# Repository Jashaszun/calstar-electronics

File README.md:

# calstar-electronics
The overall repository for CalSTAR-related hardware, firmware, software, and electronics documentation.

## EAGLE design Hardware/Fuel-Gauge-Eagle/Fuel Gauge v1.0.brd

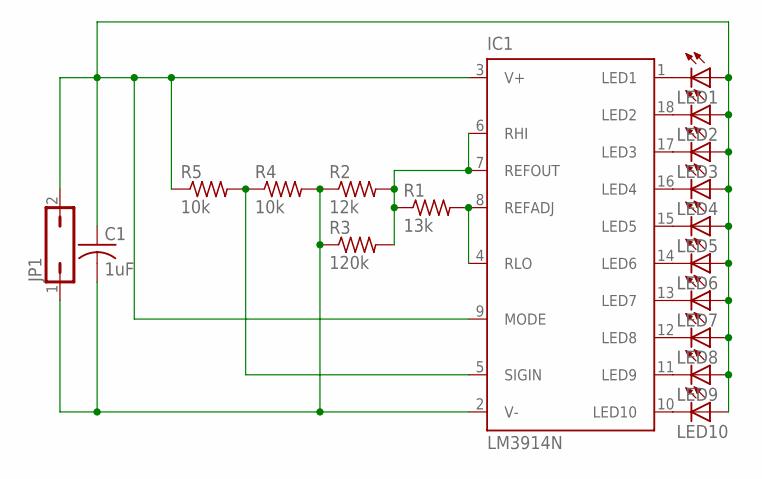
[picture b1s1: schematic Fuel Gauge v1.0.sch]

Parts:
C1: 1uF; C0603
IC1: LM3914N; DIL18
JP1: JP1Q; JP1
LED1, LED2, LED3, LED4, LED5, LED6, LED7, LED8, LED9, LED10: LEDCHIPLED_0603; CHIPLED_0603
R1: 13k; R0603
R2: 12k; R0603
R3: 120k; R0603
R4, R5: 10k; R0603

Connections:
GND: C1.2, IC1.2 (V-), JP1.1, R2.1, R3.1, R4.2
LED1: IC1.1 (LED1), LED1.C
LED2: IC1.18 (LED2), LED2.C
LED3: IC1.17 (LED3), LED3.C
LED4: IC1.16 (LED4), LED4.C
LED5: IC1.15 (LED5), LED5.C
LED6: IC1.14 (LED6), LED6.C
LED7: IC1.13 (LED7), LED7.C
LED8: IC1.12 (LED8), LED8.C
LED9: IC1.11 (LED9), LED9.C
LED10: IC1.10 (LED10), LED10.C
REFADJ/RLO: IC1.4 (RLO), IC1.8 (REFADJ), R1.2
REFOUT/RHI: IC1.6 (RHI), IC1.7 (REFOUT), R1.1, R2.2, R3.2
SIGIN: IC1.5 (SIGIN), R4.1, R5.2
VBATT: C1.1, IC1.3 (V+), IC1.9 (MODE), JP1.2, LED1.A, LED2.A, LED3.A, LED4.A, LED5.A, LED6.A, LED7.A, LED8.A, LED9.A, LED10.A, R5.1

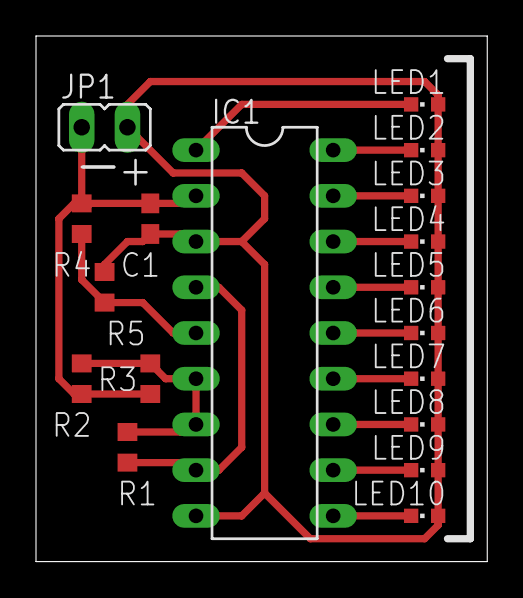
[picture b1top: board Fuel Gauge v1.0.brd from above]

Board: 2 copper layers, 25.1 x 29.2 mm, 18 parts (0 on the bottom side), 15 nets.

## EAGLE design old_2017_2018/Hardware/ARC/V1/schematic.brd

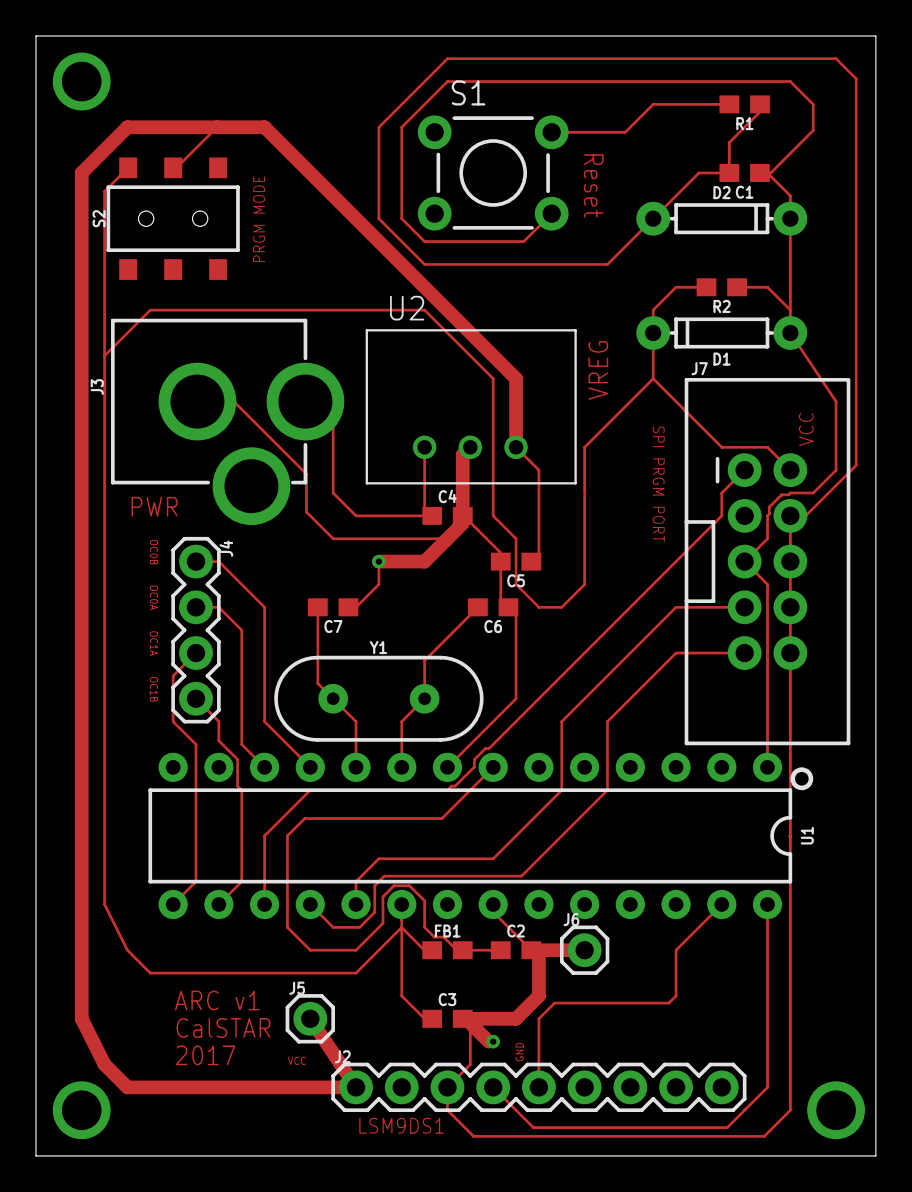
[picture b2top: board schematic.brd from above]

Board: 2 copper layers, 46.7 x 62.2 mm, 23 parts (0 on the bottom side), 18 nets.

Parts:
C1, C2, C3: 0.1uF; 0603
C4, C5: 10uF; 0603
C6, C7: 22pF; 0603
D1, D2: 200mA/100V/1V; DIODE-1N4148
FB1: 30Ω/1.8A; 0603
J2: 1X09
J3: POWER_JACK; POWER_JACK_PTH
J4: 1X04
J5, J6: 1X01
J7: 2X5-SHROUDED
R1: 330; 0603
R2: 4.7k; 0603
S1: TACTILE-PTH
S2: SWITCH_DPDT_SMD_AYZ0202
U1: 328P; DIP28
U2: R-78E5.0-1.0; DC-DC_CONVERTER_78XX
Y1: 16MHz; HC49US

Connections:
GND: C1.2, C2.2, C3.2, C4.2, C5.2, C6.1, C7.1, D2.A, J2.3, J3.GND, J6.1, J7.4, J7.6, J7.8, J7.10, R1.1, U1.8, U1.22, U2.GND
unnamed: J2.4, U1.28
unnamed: J2.5, U1.27
unnamed: J7.9, U1.18
unnamed: J7.1, U1.17
unnamed: C4.1, J3.PWR, U2.VIN
unnamed: J7.7, U1.19
unnamed: C1.1, D1.A, D2.C, J7.5, R2.1, S1.4, U1.1
unnamed: R1.2, S1.2
unnamed: J4.1, U1.11
unnamed: C5.1, J2.1, J5.1, S2.2, U2.VOUT
unnamed: C3.1, D1.C, FB1.1, J7.2, R2.2, S2.1, U1.20
unnamed: J4.2, U1.12
unnamed: C2.1, FB1.2, U1.7
unnamed: J4.3, U1.15
unnamed: J4.4, U1.16
unnamed: C6.2, U1.9, Y1.2
unnamed: C7.2, U1.10, Y1.1

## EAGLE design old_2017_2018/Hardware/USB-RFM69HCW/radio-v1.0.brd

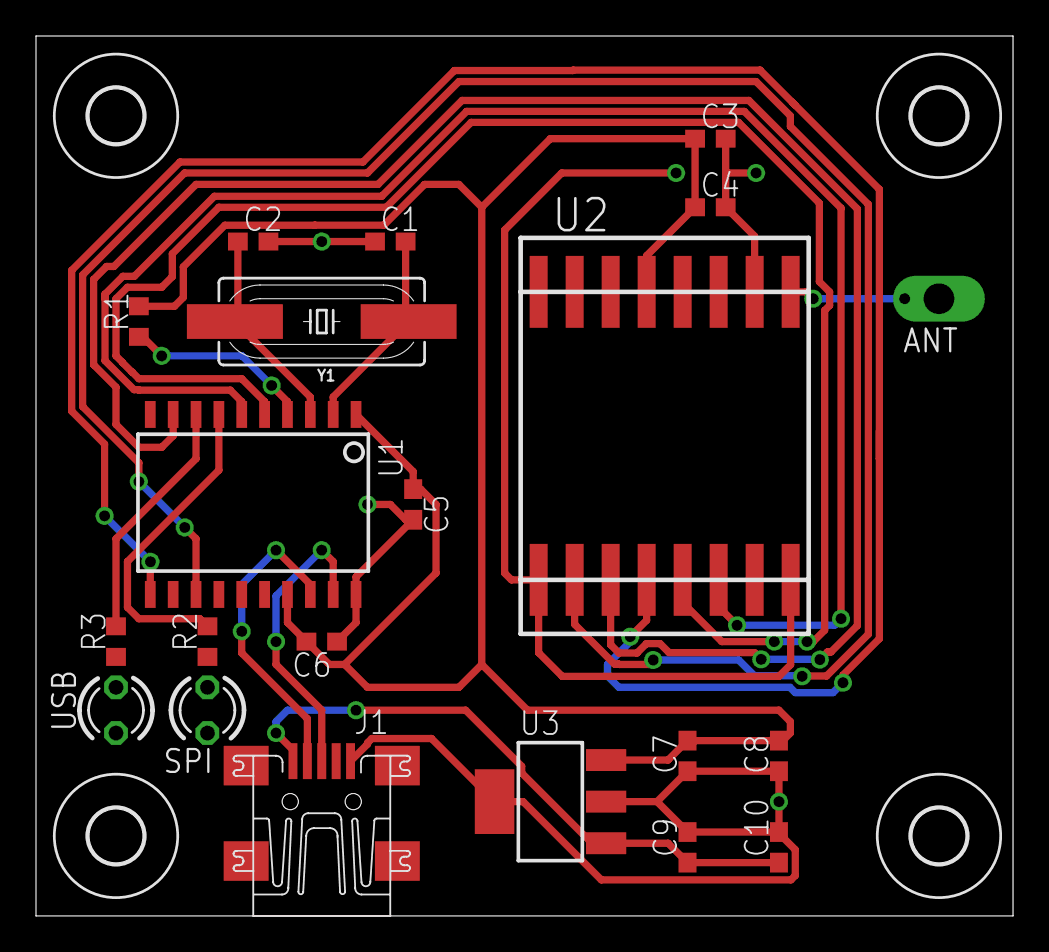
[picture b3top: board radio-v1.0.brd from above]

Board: 2 copper layers, 54.3 x 48.9 mm, 25 parts (0 on the bottom side), 18 nets.

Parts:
ANT: TPPAD1-17Y; P1-17Y
C1, C2: 20pF; C0603
C3: 10uF; C0603
C4, C5, C7, C9: 0.1uF; C0603
C6: 1uF; C0603
C8: 22uF; C0603
C10: 4.7uF; C0603
J1: MINI-USB-UX60-MB-5ST; UX60-MB-5ST
R1: 390; R0603
R2, R3: 1k; R0603
SPI: LED3MM
U1: MCP2210; SOIC20S
U2: RFM69HCW
U3: MCP1825S_DBMCP1825S_DB; SOT223
U$4, U$5, U$6, U$7: 3,0
USB: LED3MM
Y1: 12MHz; HC49UP

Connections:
5V: C9.1, C10.1, J1.1, U3.1
+3V3: C3.1, C4.1, C5.1, C6.2, C7.1, C8.1, R1.2, U1.1, U1.17, U2.P$13, U3.3
ANT: ANT.TP, U2.P$9
CS: U1.5, U2.P$5
D+: J1.3, U1.19
D-: J1.2, U1.18
GND: C1.1, C2.2, C3.2, C4.2, C5.2, C6.1, C7.2, C8.2, C9.2, C10.2, J1.5, SPI.K, U1.20, U2.P$1, U2.P$8, U2.P$10, U3.2, U3.4, USB.K
MISO: U1.13, U2.P$2
MOSI: U1.9, U2.P$3
unnamed: R2.1, SPI.A
unnamed: R3.1, USB.A
unnamed: R2.2, U1.7
unnamed: R3.2, U1.8
OSC1: C1.2, U1.2, Y1.1
OSC2: C2.1, U1.3, Y1.2
RST_RFM: U1.6, U2.P$6
RST_USB: R1.1, U1.4
SCK: U1.11, U2.P$4

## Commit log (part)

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2018-03-14 Jank connection is now fully functional and integrated
2018-03-14 i forgot flippin semicolons
2018-03-14 added wiring_analog back
2018-03-14 this test probably doesn't work
2018-03-14 pin mappings for 644p
2018-03-15 rebase is feking me
2018-03-15 644p tests
2018-03-16 Ejection fixes - UNTESTED
2018-03-17 Added ground test skeleton
2018-03-17 added uart debugging output to ultrasonic tests
2018-03-17 debugged ultrasonic tests
2018-03-18 added MightyCore arduino core with libraries, configured makefile for rover to use new libs
2018-03-18 fixed compile errors in servo_test
2018-03-18 updated pins'
2018-03-18 fixed typos in makefile
2018-03-18 stepper motors work!
2018-03-18 fixed another typo in makefile base
2018-03-18 updated pins
2018-03-18 indentation
2018-03-19 current rover test files with arduino core functions
2018-03-22 Updated PWM values for 755MG
2018-03-22 updated MC servo library to work, also added rover_basic.cpp for use at upcoming launch
2018-03-23 Update servo_test.cpp
    updated servo_test to operate all servos
2018-04-10 propulsion ejection board radio <--> uart passthrough
2018-04-28 updating arduino code to not have limits
2018-04-28 updated arduino code to be nicer
2018-09-16 start telemetry server
2018-09-22 added access control headers; more detailed spec comments
2018-10-01 Created ground propulsion project and added schematic in hardware folder.
2018-10-02 VERY basic demo of uploading and adding to database.
2018-10-02 remove lokijs, mysql and mariadb libraries to unstuck my npm install
2018-10-03 Lint automatic fixes
2018-10-03 fixed style and did some refactoring (server crashes on upload though)
2018-10-04 Updates and added Mustache for front-end template engine
2018-10-08 Starting on SIL
2018-10-11 Added JSON parsing for motor
2018-10-11 Removed extra files, added gitignore
2018-10-12 Works with basic rocket
2018-10-14 Added pinMode support
2018-10-18 added ground_systems folder
2018-10-18 Added sil outputs and other stuff
2018-10-21 ported RFM69 to DipTrace
2018-10-21 add component lib to top level folder
2018-10-22 initial commit of black box component library
2018-10-22 added decoupling
2018-10-22 set up supplies and decoupling caps
2018-10-22 added power section
2018-10-22 add leds, buttons, and a debug header
2018-10-22 fixed supply decoupling on VDDA
2018-10-22 added fc schematic
2018-10-23 added GPS
2018-10-23 Engine and Telemetry UARTs
2018-10-23 schematic and updated libraries
2018-10-23 added UART from GPS to MCU
2018-10-23 Added black powder port to FC schematic.
2018-10-25 separated booster and sustainer schematics
2018-10-25 added component for transistor
2018-10-28 fix decoupling cap on vbat, move ferrite bead
2018-10-28 Adding multiple MCU support
2018-10-28 added buttons and stuff part 2
2018-10-29 new transistor
2018-10-29 updated GPS to ver 3
2018-10-29 added descriptions
2018-10-29 need review
2018-10-30 Added initial schematic for propulsion ground test dejankification board.
2018-10-30 antenna-radio connection fixes
2018-10-30 Revert "Ground propulsion: ground test dejankification board schematic"
2018-10-31 added KX222 footprint
2018-10-31 add molex fpc connector
2018-10-31 fixed pad mapping on regulator
2018-11-01 some footprints added
2018-11-01 components
2018-11-01 fixes from pr feedback
2018-11-01 Added GPS schematic component
2018-11-01 Moved GPS updates to booster T/PC schematic
2018-11-01 deleted power_telemetry_schematic
2018-11-01 Added temp library for testing
2018-11-01 Added transistor footprint
2018-11-01 copied transistor footprint into STAR library
2018-11-01 updated programming port symbol
2018-11-01 Fix capacitor values, only use one LED
2018-11-01 changed IMU decoupling cap and added a ground on IMU FSYNC pin
2018-11-02 adding RS422 footprint and schematic symbol
2018-11-02 slight verification warning fixes
2018-11-02 Added SMA footprint
2018-11-02 Updated GPS footprint to have pins instead of mounting holes
2018-11-02 added molex symbol
2018-11-02 hooked rs422 up to molex
2018-11-02 Add molex 2-pin connector
2018-11-02 Initial layout work
2018-11-02 added MPL footprint
2018-11-02 added MPU-9250 footprint
2018-11-03 Added RS422, reset, programmer
2018-11-03 Added inductor footprint
2018-11-03 minor changes
2018-11-03 added footprints for electrolytic capacitors
2018-11-03 named a few more nets, connected black powder to microcontroller
2018-11-03 layout complete. Now working on silk
2018-11-03 touch up schematic and do daughter board layout
2018-11-03 About to go to layout
2018-11-03 added files for logos
2018-11-03 touch up daughter board layout, and start on blackbox layout
2018-11-03 Make initial version of blackbox layout
2018-11-03 added missing passives for transistor
2018-11-03 Updated flight computer schematic
2018-11-04 Finished flight computer schematic hopefully
2018-11-04 Minor flight computer update
2018-11-04 fixed some bad connections
2018-11-04 Layout in progress
2018-11-04 made trace angles smoother
2018-11-04 add double sided board
2018-11-04 Fix some issues
2018-11-04 fixed overtoleranced mpu on doublesided bb
2018-11-04 add mounting holes
2018-11-04 added dimenshioning
2018-11-04 lots of tracing
2018-11-04 first iteration of layout
2018-11-04 More trace work
2018-11-04 changed ring sizes. added new pours and edge cut
2018-11-04 More traces
2018-11-05 readded some pins, made pour into ground
2018-11-05 data points can get deleted now
2018-11-05 Just noticed I made this and previous commits with the wrong email. Should be fixed now.
2018-11-05 Schematic debugging UART, power LED, and photodiode
2018-11-06 Added black powder circuitry with schematic and footprints.
2018-11-06 fixed photodiode connection, debug UART; waiting on jacob to possibly choose IC for BP
2018-11-06 Changed black powder to a monolothic IC.
2018-11-06 Removed temp black powder stuff and added pull-downs on ignition lines.
2018-11-06 Black powder ICs connected
2018-11-07 named a bunch of nets
2018-11-07 began routing bp, decided to move voltage reg to middle of board
2018-11-07 forgot to commit schematic on prev commit
2018-11-07 rename rgb led to 'state led'
2018-11-07 Added full Arduino shield component and more of schematic.
2018-11-07 started bp connections on layout, rotated microcontroller
2018-11-07 fix pours
2018-11-07 Added shield footprint.
2018-11-07 Maybe done
2018-11-08 In the middle of replacing BP headers
2018-11-08 Added labels and mounting holes
2018-11-08 fixing power block
2018-11-08 Added CSV export endpoint
2018-11-08 split up power lines
2018-11-08 Made ground test setup board! Passes verifications and DFM.
2018-11-08 layout v2 complete
2018-11-08 added calstar logo
2018-11-08 Added user creation and login. Sessions not implemented yet.
2018-11-08 Added session support and administrator authorization control. Warning: not secure.
2018-11-09 fixed silkscreen
2018-11-09 fix spelling
2018-11-09 added spi debug board
2018-11-09 length matched tx rx lines, added GPS mounting holes, removed board edge footprint
2018-11-09 fixed diode pad size
2018-11-09 fixed copper pour under diode pad
2018-11-09 fixed uart vcc to be to 5v
2018-11-09 some pour changes
2018-11-10 fixed powerpole orientations, straightened pours, moved mountint holes
2018-11-10 deleted old layout file
2018-11-11 soft deletion
2018-11-11 Users can now be pre-authorized by email address
2018-11-11 fixed soft deletion; now saves CSV files
2018-11-11 silkscreen and via changes
2018-11-11 now passes DRC
2018-11-11 Defaults to creating new run, updated upload instructions. Fixes #73
2018-11-11 quick merge
2018-11-11 added RstEn silk
2018-11-12 Modified setup and authorize commands
2018-11-12 connected nets
2018-11-12 fix battery connector
2018-11-12 expanded top-level ground pour on TPC
2018-11-12 Flight computer final-final
2018-11-12 add logos
2018-11-12 finalfinalfinalfinal
2018-11-12 maybe add copper bear
2018-11-12 move bear
2018-11-12 Moved powerpole to side
2018-11-12 add model for connector
2018-11-12 moved antenna 1 F***ING MIL
2018-11-12 forgot to remove a log
2018-11-12 made board points rectangular
2018-11-12 cut width from 3.61 in to 3.3 in
2018-11-12 flipped molex connectors
2018-11-12 fixed silkscreen, renamed layout file
2018-11-12 removed temp files, deleted transistor Rin resistors
2018-11-13 resurrected b* image files
2018-11-13 fixed debug uart silk
2018-11-13 updated reset button silk and net names
2018-11-13 fixed RIGHT ANGLE HISSSSS
2018-11-13 Updated silk
2018-11-13 added some via stitching to flight computer
2018-11-13 determined LED resistor values
2018-11-13 removed COMIC SANS
2018-11-13 fixed silks and refdes (and got rajiv's changes)
2018-11-14 added LED resistor values
2018-11-14 changed some part values
2018-11-14 added blackbox gerbers
2018-11-14 added fc gerbers
2018-11-14 added ground prop gerbers
2018-11-14 added tpc gerbers
2018-11-16 Added resistor values.
2018-11-19 added mbed port of radio library from last year
2018-11-19 initial ground station firmware
2018-11-22 make 3d models better
2018-11-22 fix header offset in model
2018-11-24 formatting
2018-11-25 remove ferrite bead
2018-11-25 fix rst header pin directions, flipped silk on engine rs422
2018-11-25 copied over overview from gitbooks, and linked to gitbooks
2018-11-25 removed old names
2018-11-26 added measurements to layout and reorganized schematic
2018-11-28 Moved ground prop hardware libraries to lib/ folder
2018-12-04 added pin definitions
2018-12-05 testing ground station
2018-12-05 added value labels on inductors; rename software to firmware
2018-12-10 pulled external dependencies
2019-01-15 Updated 22 uH footprint
2019-01-16 moved port 3 to pb8
2019-01-16 fixed error where GPS pins were changed to SMD
2019-01-17 temp
2019-01-18 redid switching regulator layout
2019-01-19 compacted things
2019-01-24 weird trace fixed
2019-01-24 adding tests
2019-01-24 adding everything in ground sys
2019-01-26 test. failed
2019-01-26 Rainbow LED test program
2019-01-30 better rfm lib?
2019-01-30 Debug printing altimeter read (MODIFIES LIBARRY, SHOULD REVERT EVENTUALLY), blackbox testing easier
2019-02-09 updated programming port pattern
2019-02-09 updated blackbox schematic
2019-02-10 grounded boot0 and boot1 through 10k resistors. removed many decoupling caps. programming header has nrst instead of njtrst. added shield to usb (grounded). added swo to programming header.
2019-02-10 updated resistor values
2019-02-10 added testpoints
2019-02-10 increased version number to v3.2
2019-02-10 showed boot pin resistor values
2019-02-12 add daughter board jumpers and fix connections on main board
2019-02-13 add swo
2019-02-13 blackbox layout update
2019-02-13 Removed engine controller from schematic
2019-02-13 moved regulator, keyswitch is now a powerpole
2019-02-24 re-org'd github now that hardware is on grabcad
2019-02-24 adding test projects
2019-02-24 now includes io3 (previously on boot0), fixed LOG to printf
2019-02-27 Users now able to upload AND VIEW their data.
    The data has been transposed so it can be viewed in a more intuitive way. They can add as many variables (columns) and rows as they want. However, graphing using Plot.js broke. Also, the authorizatio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
2019-03-03 Removed tests from fc branch, moving to calstar/firmware-tests
2019-03-05 Added flatbuffers
2019-03-05 flatbuf
2019-03-06 updated groundstation code to new rfm lib
2019-03-06 removed mbed_settings.pyc from tracking
2019-03-06 added openmct stuff
2019-03-08 removed sleep after send
2019-03-10 added tx and rx led code
2019-03-11 More fixes
2019-03-11 Added Dtr enable in RadioSerial.
2019-03-16 usb test
2019-04-12 Added initial live text updates to console
2019-04-12 sync time based on first received timestamp from gs
2019-04-12 Added live text updates
2019-04-13 package updates
2019-04-13 merged
2019-04-15 Added automatic port finding
2019-04-15 Changed automatic COM port check
2019-04-15 Added important comment
2019-04-15 gs openmct
2019-04-15 moving average battery and openmct
2019-04-17 Added transmit lockout message.
2019-04-17 Elements no longer sorted lexigraphically, and download function works.
2019-04-17 added make layouts

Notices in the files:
parts and their libraries:
SparkFun-Capacitors: Licensing: Creative Commons ShareAlike 4.0 International - https://creativecommons.org/licenses/by-sa/4.0
